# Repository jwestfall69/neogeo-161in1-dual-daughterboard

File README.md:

# neogeo-161in1-dual-daughterboard

  * [Overview](#overview)
  * [PCB Manufacturing](#pcb-manufacturing)
  * [Parts](#parts)
  * [Soldering](#soldering)
  * [Programming](#programming)
  * [What to flash](#what-to-flash)
  * [Install](#install)

## Overview
Vortex's [VTXCart](https://github.com/xvortex/VTXCart/tree/main) project allows rewriting the flash/CPLD chips on the 161in1 V3 cart to contain whatever neogeo games you want.  However there isn't enough C flash space on a stock 161in1 cart to handle the entire neogeo library.  

The C (and V) flash chips come on small daughterboards, one flash chip per daughterboard.  This dual daughterboard project is a replacement daughterboard that adds support for 2 flash chips on the daughterboard.  This allows increasing the available C flash space from 2G to 3G, which make possible to have the entire neogeo library on the cart.

**NOTE:** This has only been tested on the MVS version of the 161in1 V3 cart.  I have not seen the inside of the AES version to know if the dual daughterboard can fit.

**Bare Boards:**<br>

**Assembled Top/Bottom:**<br>

## PCB Manufacturing
You should select board thickness of 0.8mm.

The board has very fine pitched (0.8mm) castellated holes on it.  Ideally you would want to pick the castellated holes option with the PCB manufacture so they get cut cleanly.  However the PCB manufacturer will likely reject the order if you pick the option because most require 0.6mm hole diameter and 0.6mm distance between castellated holes.

Placing the order without the castellated holes option should go through but will cause the holes to be slightly mangled and look something like this.

You can see how the copper from the left side of the through hole is still there just kinda push flat against the cut path.  To fix this you can use fine tipped tweezers to push that extra copper into the right side of the hole.  It should end up looking something like this, which is good enough.

Don't attempt to pull the extra copper off or you could rip out all of the copper from the through hole.

Once done, I would suggest using a magnifying glass to verify you see raw pcb between each of the castellated holes.

## Parts
The 2x F0095H0 flash chips will need to come from a 161in1 board as they don't seem to be something you can just buy.

The dip male connectors are dual row 1.27mm, 22 pins per row, 44 pins total per connector.  Best bet is to just by some cheap 2x50 pin connectors and cut them down to size.

## Soldering
I'm going to assume you don't really need soldering advice if you are taking on the task of making a VTXCart.  But I will warn you to be careful when soldering the dip connector.  It doesn't seem to take much heat and side pressure to cause the individual pins to shift around and you can end up with pins pointing all over the place instead of 2 straight lines.

## Programming
One thing you need to consider is how you are going to program the flash chips.  

With only U1 flash chip installed the dual daughterboard will act the same as a normal daughterboard for reading/writing.  So you can use Vortex's F0095H0 dumper board to program it.

However the flash chip that will installed into U2 will need to be flashed by something else.  Ideally you should use the original daughterboard it came on with the F0095H0 dumper board.

## What to flash
Running vortex's compiler program with the 'c3g' option will increase the available C rom space to 3G.  When completed it should have generated 3 crom files.  They need to be flashed as follows.

crom-1 = U1 on dual daughterboard<br>
crom-2 = normal daughterboard (installed in the left most C rom daughterboard location, as seen below)<br>
crom-3 = U2 on dual daughterboard<br>

## Install
The original daughterboards are soldered to the CHA/PROG boards.  As part of creating a VTXCart you should be installing female connectors to make the daughterboards plugable as seen here.

These female connectors are require for the dual daughterboard to fit properly.  Trying to solder it directly to the CHA board will cause you to run into clearance issues with the CPLD.

The dual daughterboard must be installed into the right most C rom daughterboard location.  Its not possible for it to be installed in the left location because it would collide with the white board to board connector on the back of the PROG board.  This is also why you can't do 4G of C rom space (not that there would be a need to have that much).

The OE1 and OE2 pins on the dual daughterboard need to be soldered to pins on the CPLD.  As of right now the allocated pins are

AES:
  * OE1 = PIN 48
  * OE2 = PIN 47

MVS
  * OE1 = PIN 31
  * OE2 = PIN 30

You should however verify this is still the case by looking at the pin assignments for the CHA_CP1 CPLD in the VTXCart project.  Look for ```C3_nOE[0]``` (OE1) and ```C3_nOE[1]``` (OE2) under Assignments -> Pin Planner in Quartus.

Fully installed it should looks like this (MVS)

Lastly an adjustment needs to be made to the bends of board the board cable to make space for the dual daughterboard.

This is what it normally looks like (back of PROG board):

This is what it will need to be adjusted to:

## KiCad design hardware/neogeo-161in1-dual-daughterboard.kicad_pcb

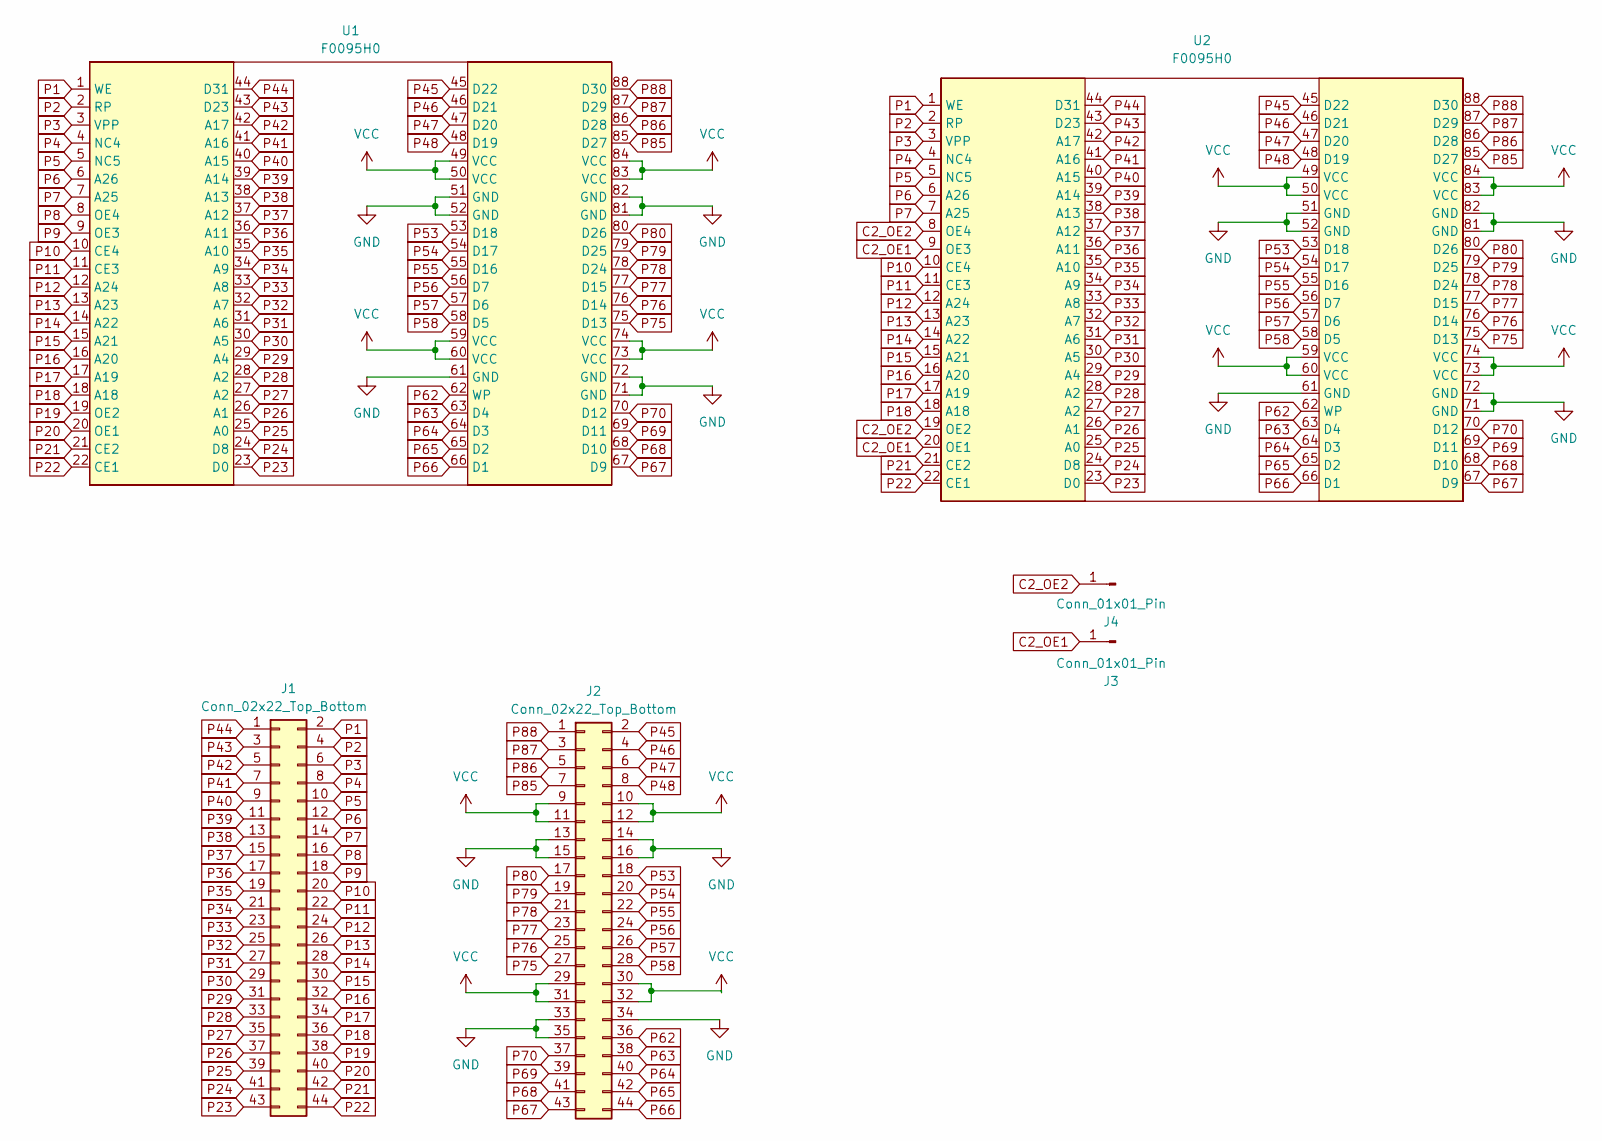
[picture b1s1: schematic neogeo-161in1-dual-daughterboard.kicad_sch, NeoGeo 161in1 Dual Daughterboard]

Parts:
J1, J2: Conn_02x22_Top_Bottom; PinHeader_2x22_P1.27mm_Vertical
J3, J4: Conn_01x01_Pin; TestPoint_Pad_D1.5mm
U1, U2: F0095H0

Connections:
C2_OE1: J3.1, U2.9 (OE3), U2.20 (OE1)
C2_OE2: J4.1, U2.8 (OE4), U2.19 (OE2)
GND: J2.13, J2.14, J2.15, J2.16, J2.33, J2.34, J2.35, U1.51 (GND), U1.52 (GND), U1.61 (GND), U1.71 (GND), U1.72 (GND), U1.81 (GND), U1.82 (GND), U2.51 (GND), U2.52 (GND), U2.61 (GND), U2.71 (GND), U2.72 (GND), U2.81 (GND), U2.82 (GND)
P1: J1.2, U1.1 (WE), U2.1 (WE)
P2: J1.4, U1.2 (RP), U2.2 (RP)
P3: J1.6, U1.3 (VPP), U2.3 (VPP)
P4: J1.8, U1.4 (NC4), U2.4 (NC4)
P5: J1.10, U1.5 (NC5), U2.5 (NC5)
P6: J1.12, U1.6 (A26), U2.6 (A26)
P7: J1.14, U1.7 (A25), U2.7 (A25)
P8: J1.16, U1.8 (OE4)
P9: J1.18, U1.9 (OE3)
P10: J1.20, U1.10 (CE4), U2.10 (CE4)
P11: J1.22, U1.11 (CE3), U2.11 (CE3)
P12: J1.24, U1.12 (A24), U2.12 (A24)
P13: J1.26, U1.13 (A23), U2.13 (A23)
P14: J1.28, U1.14 (A22), U2.14 (A22)
P15: J1.30, U1.15 (A21), U2.15 (A21)
P16: J1.32, U1.16 (A20), U2.16 (A20)
P17: J1.34, U1.17 (A19), U2.17 (A19)
P18: J1.36, U1.18 (A18), U2.18 (A18)
P19: J1.38, U1.19 (OE2)
P20: J1.40, U1.20 (OE1)
P21: J1.42, U1.21 (CE2), U2.21 (CE2)
P22: J1.44, U1.22 (CE1), U2.22 (CE1)
P23: J1.43, U1.23 (D0), U2.23 (D0)
P24: J1.41, U1.24 (D8), U2.24 (D8)
P25: J1.39, U1.25 (A0), U2.25 (A0)
P26: J1.37, U1.26 (A1), U2.26 (A1)
P27: J1.35, U1.27 (A2), U2.27 (A2)
P28: J1.33, U1.28 (A2), U2.28 (A2)
P29: J1.31, U1.29 (A4), U2.29 (A4)
P30: J1.29, U1.30 (A5), U2.30 (A5)
P31: J1.27, U1.31 (A6), U2.31 (A6)
P32: J1.25, U1.32 (A7), U2.32 (A7)
P33: J1.23, U1.33 (A8), U2.33 (A8)
P34: J1.21, U1.34 (A9), U2.34 (A9)
P35: J1.19, U1.35 (A10), U2.35 (A10)
P36: J1.17, U1.36 (A11), U2.36 (A11)
P37: J1.15, U1.37 (A12), U2.37 (A12)
P38: J1.13, U1.38 (A13), U2.38 (A13)
P39: J1.11, U1.39 (A14), U2.39 (A14)
P40: J1.9, U1.40 (A15), U2.40 (A15)
P41: J1.7, U1.41 (A16), U2.41 (A16)
P42: J1.5, U1.42 (A17), U2.42 (A17)
P43: J1.3, U1.43 (D23), U2.43 (D23)
P44: J1.1, U1.44 (D31), U2.44 (D31)
P45: J2.2, U1.45 (D22), U2.45 (D22)
P46: J2.4, U1.46 (D21), U2.46 (D21)
P47: J2.6, U1.47 (D20), U2.47 (D20)
P48: J2.8, U1.48 (D19), U2.48 (D19)
P53: J2.18, U1.53 (D18), U2.53 (D18)
P54: J2.20, U1.54 (D17), U2.54 (D17)
P55: J2.22, U1.55 (D16), U2.55 (D16)
P56: J2.24, U1.56 (D7), U2.56 (D7)
P57: J2.26, U1.57 (D6), U2.57 (D6)
P58: J2.28, U1.58 (D5), U2.58 (D5)
P62: J2.36, U1.62 (WP), U2.62 (WP)
P63: J2.38, U1.63 (D4), U2.63 (D4)
P64: J2.40, U1.64 (D3), U2.64 (D3)
P65: J2.42, U1.65 (D2), U2.65 (D2)
P66: J2.44, U1.66 (D1), U2.66 (D1)
P67: J2.43, U1.67 (D9), U2.67 (D9)
P68: J2.41, U1.68 (D10), U2.68 (D10)
P69: J2.39, U1.69 (D11), U2.69 (D11)
P70: J2.37, U1.70 (D12), U2.70 (D12)
P75: J2.27, U1.75 (D13), U2.75 (D13)
P76: J2.25, U1.76 (D14), U2.76 (D14)
P77: J2.23, U1.77 (D15), U2.77 (D15)
P78: J2.21, U1.78 (D24), U2.78 (D24)
P79: J2.19, U1.79 (D25), U2.79 (D25)
P80: J2.17, U1.80 (D26), U2.80 (D26)
P85: J2.7, U1.85 (D27), U2.85 (D27)
P86: J2.5, U1.86 (D28), U2.86 (D28)
P87: J2.3, U1.87 (D29), U2.87 (D29)
P88: J2.1, U1.88 (D30), U2.88 (D30)
VCC: J2.9, J2.10, J2.11, J2.12, J2.29, J2.30, J2.31, J2.32, U1.49 (VCC), U1.50 (VCC), U1.59 (VCC), U1.60 (VCC), U1.73 (VCC), U1.74 (VCC), U1.83 (VCC), U1.84 (VCC), U2.49 (VCC), U2.50 (VCC), U2.59 (VCC), U2.60 (VCC), U2.73 (VCC), U2.74 (VCC), U2.83 (VCC), U2.84 (VCC)

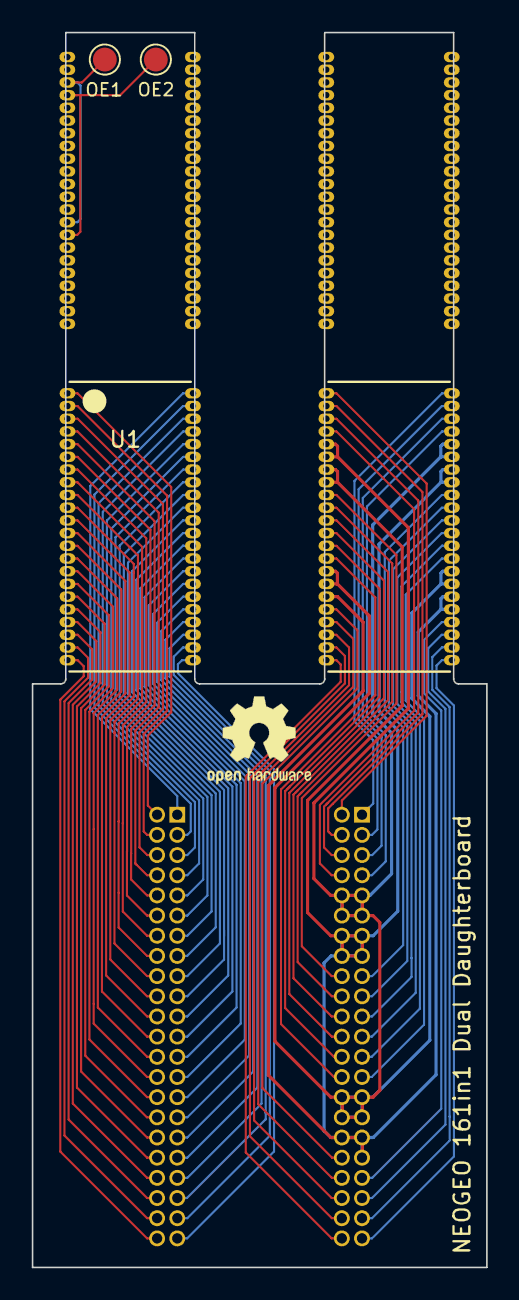
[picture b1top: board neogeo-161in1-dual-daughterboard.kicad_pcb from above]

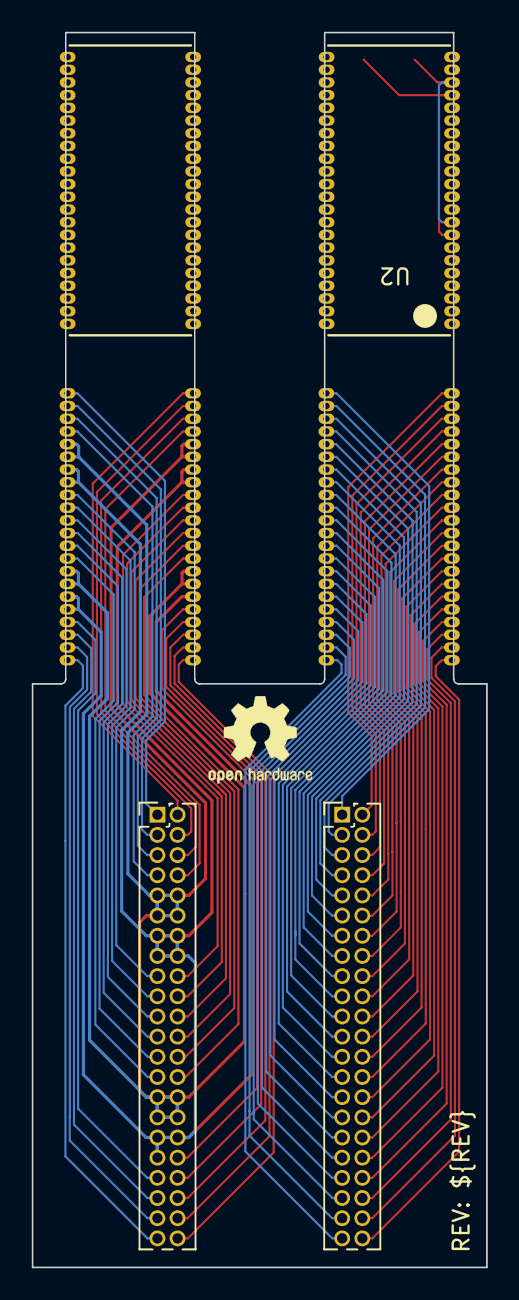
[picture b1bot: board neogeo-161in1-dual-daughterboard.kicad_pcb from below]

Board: 4 copper layers, 28.6 x 77.7 mm, 6 parts (3 on the bottom side), 77 nets.

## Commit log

2023-10-07 Doc updates
